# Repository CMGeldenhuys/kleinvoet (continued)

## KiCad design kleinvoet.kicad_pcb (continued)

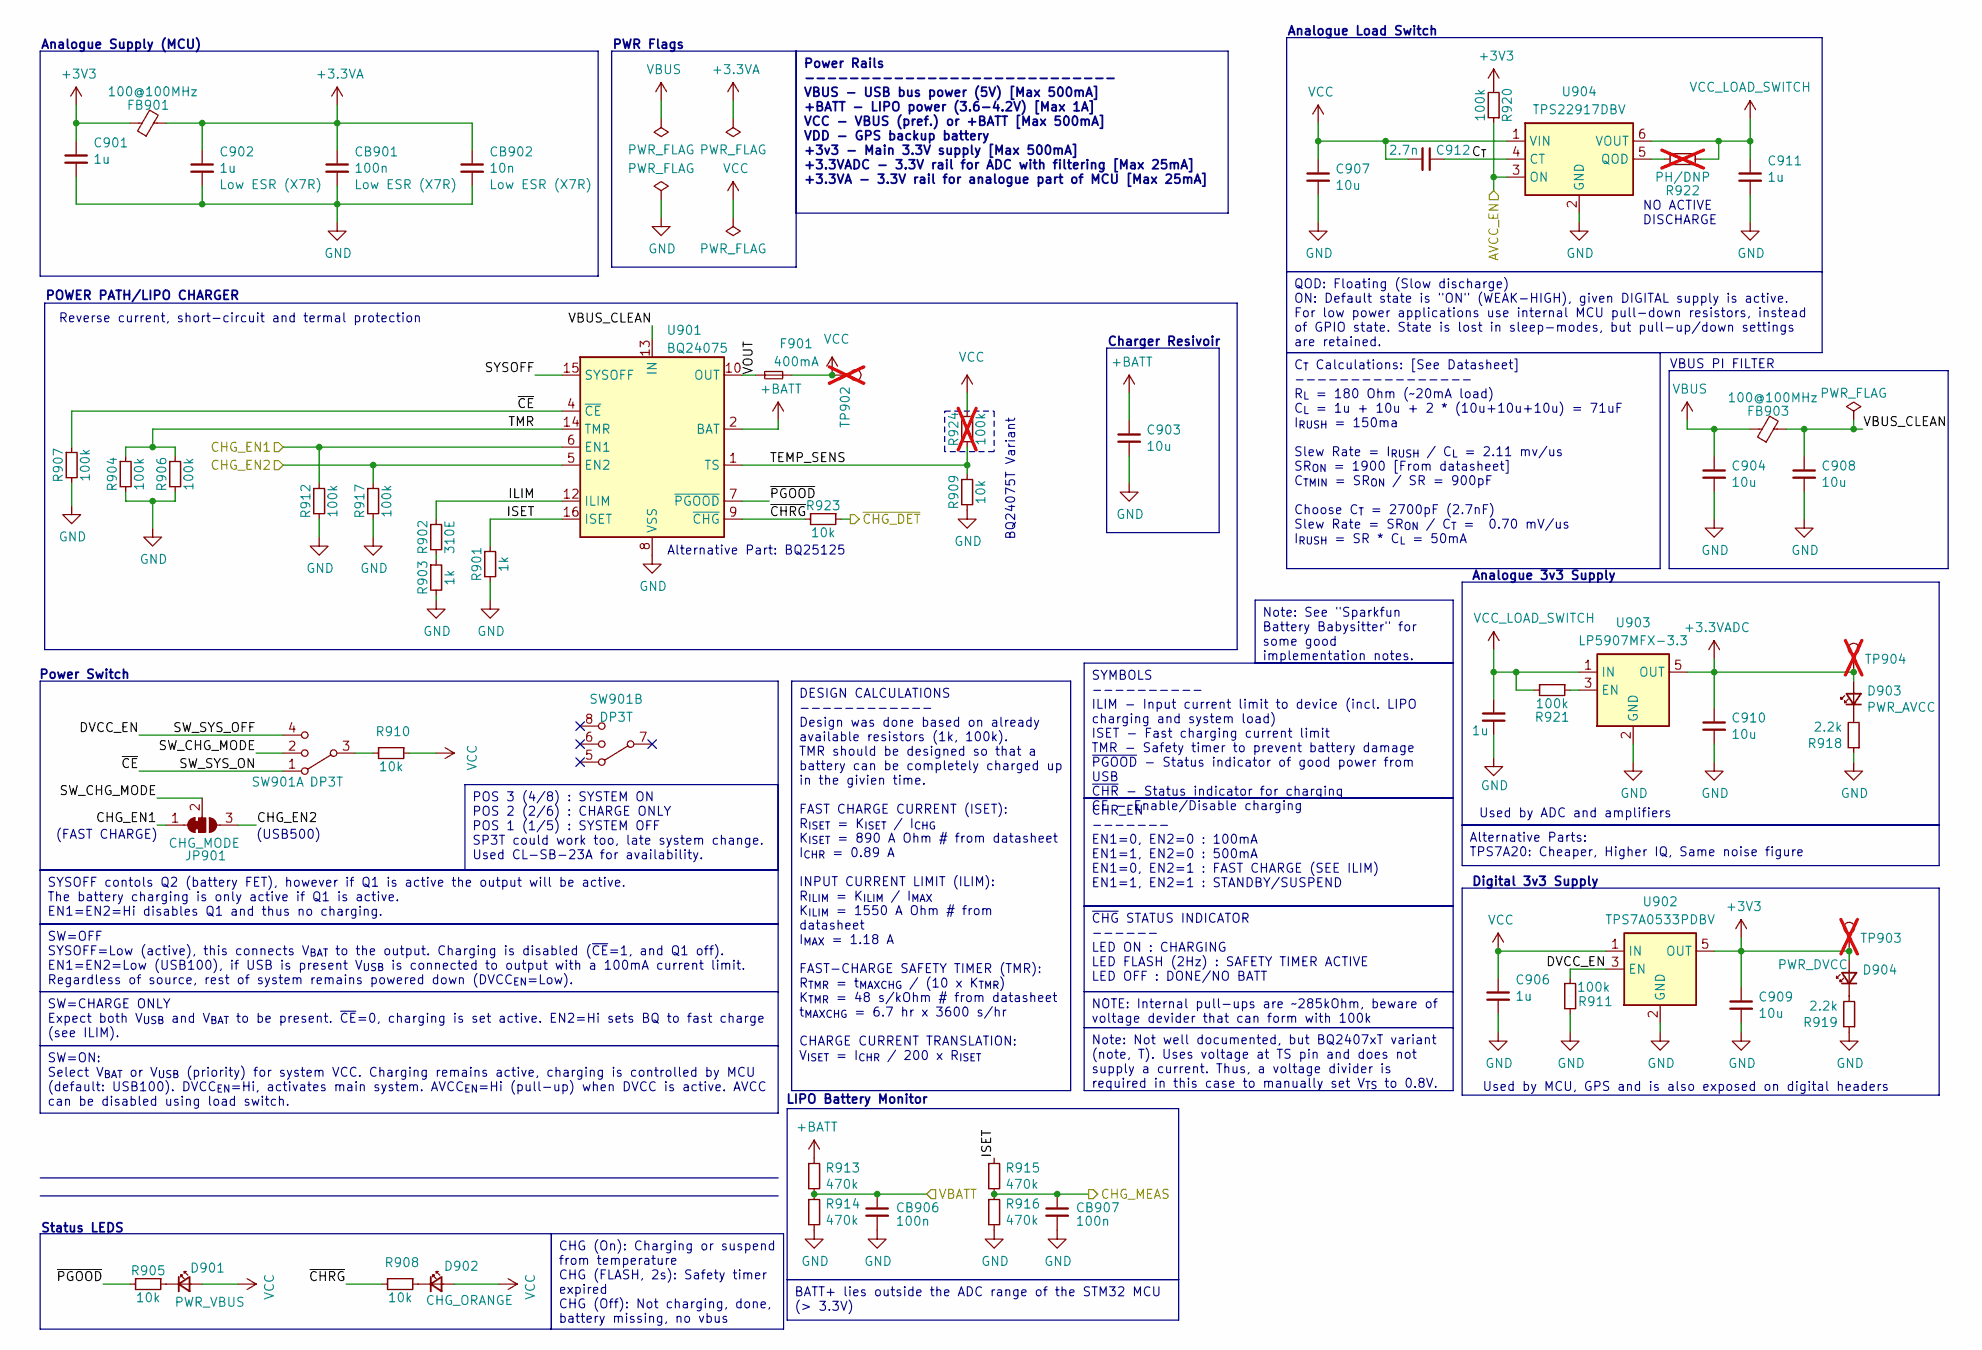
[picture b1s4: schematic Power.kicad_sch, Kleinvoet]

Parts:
C901, C902, C905, C906, C911: 1u; C_0402_1005Metric; MPN C0402C105K9PACTU
C903, C904, C907, C908, C909, C910: 10u; C_0402_1005Metric; MPN GRM155R60J106ME05D
C912: 2.7n; C_0402_1005Metric; MPN GRM1555C1H272GE01D
CB901, CB906, CB907: 100n; C_0402_1005Metric; MPN C0402C104K8PACTU
CB902: 10n; C_0402_1005Metric; MPN C0402C103K3RAC7411
D901: PWR_VBUS; LED_0603_1608Metric; MPN SML-D12U8WT86C
D902: CHG_ORANGE; LED_0603_1608Metric; MPN SML-D12D8WT86C
D903: PWR_AVCC; LED_0603_1608Metric; MPN SML-D12U8WT86C
D904: PWR_DVCC; LED_0603_1608Metric; MPN SML-D12U8WT86C
F901: 400mA; Fuse_0603_1608Metric_Pad1.05x0.95mm_HandSolder; MPN 0ZCM0020FF2G
FB901, FB903: 100@100MHz; L_0402_1005Metric; MPN BLM15HD102SN1D
JP901: CHG_MODE; SolderJumper-3_P1.3mm_Bridged12_RoundedPad1.0x1.5mm_NumberL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
R901, R903: 1k; R_0402_1005Metric; MPN RT0402FRE071KL
R902: 310E; R_0402_1005Metric; MPN RT0402FRE07309RL
R904, R906, R907, R911, R912, R917, R920, R921: 100k; R_0402_1005Metric; MPN RT0402FRE07100KL
R905, R908, R909, R910, R923: 10k; R_0402_1005Metric; MPN RT0402FRE1310KL
R913, R914, R915, R916: 470k; R_0603_1608Metric; MPN RC0603FR-07470KL
R918, R919: 2.2k; R_0402_1005Metric; MPN RT0402FRE072K2L
R922: PH/DNP; R_0402_1005Metric; not fitted
R924: 100k; R_0402_1005Metric; MPN RT0402FRE07100KL; not fitted
SW901: DP3T; SW_DP3T_Nidec-Cobal_CL-SB-23A; MPN CL-SB-23A-11T
TP902: V_OUT; TestPoint_Pad_D1.0mm; not fitted
TP903: 3V3_DIGITAL; TestPoint_Pad_D1.0mm; not fitted
TP904: 3v3_ANALOG; TestPoint_Pad_D1.0mm; not fitted
U901: BQ24075; VQFN-16-1EP_3x3mm_P0.5mm_EP1.68x1.68mm_ThermalVias; MPN BQ24075RGTR
U902: TPS7A0533PDBV; SOT-23-5; MPN TPS7A0533PDBVR
U903: LP5907MFX-3.3; SOT-23-5; MPN LP5907MFX-3.3/NOPB
U904: TPS22917DBV; SOT-23-6; MPN TPS22917DBVR

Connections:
+3.3VA: C902.1, CB901.1, CB902.1, FB901.2; also elsewhere on the board
+3.3VADC: C910.1, D903.2 (A), TP904.1, U903.5 (OUT); also elsewhere on the board
+BATT: C903.1, R913.1, U901.2 (BAT), U901.3 (BAT); also elsewhere on the board
/AVCC_EN: R920.1, U904.3 (ON); also elsewhere on the board
/BATT_~CHG: R923.1; also elsewhere on the board
/CHARGE_EN1: JP901.1 (A), R912.1, U901.6 (EN1); also elsewhere on the board
/CHARGE_EN2: JP901.3 (B), R917.1, U901.5 (EN2); also elsewhere on the board
/I_CHARGE: CB907.1, R915.2, R916.1; also elsewhere on the board
/Power/C_{T}: C912.1, U904.4 (CT)
/Power/DVCC_EN: R911.1, SW901.4, U902.3 (EN)
/Power/ILIM: R902.1, U901.12 (ILIM)
/Power/ISET: R901.1, R915.1, U901.16 (ISET)
/Power/SW_CHG_MODE: JP901.2 (C), SW901.2
/Power/SW_SYS_ON: R907.1, SW901.1, U901.4 (~CE)
/Power/SYSOFF: U901.15 (SYSOFF)
/Power/TEMP_SENS: R909.1, R924.2, U901.1 (TS)
/Power/TMR: R904.1, R906.1, U901.14 (TMR)
/Power/VBUS_CLEAN: C908.1, FB903.2, U901.13 (IN)
/Power/VOUT: F901.1, U901.10 (OUT), U901.11 (OUT)
/Power/~CHRG: R908.2, R923.2, U901.9 (~CHG)
/Power/~PGOOD: R905.2, U901.7 (~PGOOD)
/V_MONITOR: CB906.1, R913.2, R914.1; also elsewhere on the board
GND: C901.2, C902.2, C903.2, C904.2, C905.2, C906.2, C907.2, C908.2, C909.2, C910.2, C911.2, CB901.2, CB902.2, CB906.2, CB907.2, R901.2, R903.2, R904.2, R906.2, R907.2, R909.2, R911.2, R912.2, R914.2, R916.2, R917.2, R918.1, R919.1, U901.8 (VSS), U901.17 (VSS), U902.2 (GND), U903.2 (GND), U904.2 (GND); also elsewhere on the board
unnamed: D901.1 (K), R905.1
unnamed: D902.1 (K), R908.1
unnamed: D903.1 (K), R918.2
unnamed: D904.1 (K), R919.2
unnamed: R902.2, R903.1
unnamed: R910.2, SW901.3
unnamed: R921.1, U903.3 (EN)
unnamed: R922.1, U904.5 (QOD)
VBUS: C904.1, FB903.1; also elsewhere on the board
VCC: C906.1, C907.1, C912.2, D901.2 (A), D902.2 (A), F901.2, R910.1, R924.1, TP902.1, U902.1 (IN), U904.1 (VIN); also elsewhere on the board
VCC_LOAD_SWITCH: C905.1, C911.1, R921.2, R922.2, U903.1 (IN), U904.6 (VOUT); also elsewhere on the board

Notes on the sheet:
Status LEDS
Analogue Load Switch
Charger Resivoir
VBUS PI FILTER
Reverse current, short-circuit and termal protection
Power Switch
Digital 3v3 Supply
(FAST CHARGE)
LIPO Battery Monitor
Alternative Part: BQ25125
NO ACTIVE DISCHARGE
Analogue 3v3 Supply
PWR Flags
BQ24075T Variant
Used by ADC and amplifiers
POWER PATH/LIPO CHARGER
(USB500)
Analogue Supply (MCU)
Used by MCU, GPS and is also exposed on digital headers
Note: Not well documented, but BQ2407xT variant (note, T). Uses voltage at TS pin and does not supply a current. Thus, a voltage divider is required in this case to manually set V_{TS} to 0.8V.
SYSOFF contols Q2 (battery FET), however if Q1 is active the output will be active. The battery charging is only active if Q1 is active. EN1=EN2=Hi disables Q1 and thus no charging.
QOD: Floating (Slow discharge) ON: Default state is "ON" (WEAK-HIGH), given DIGITAL supply is active. For low power applications use internal MCU pull-down resistors, instead of GPIO state. State is lost in sleep-modes, but pull-up/down settings are retained.
SW=ON: Select V_{BAT} or V_{USB} (priority) for system VCC. Charging remains active, charging is controlled by MCU (default: USB100). DVCC_{EN}=Hi, activates main system. AVCC_{EN}=Hi (pull-up) when DVCC is active. AVCC can be disabled using load switch.
CHR_EN ------- EN1=0, EN2=0 : 100mA EN1=1, EN2=0 : 500mA EN1=0, EN2=1 : FAST CHARGE (SEE ILIM) EN1=1, EN2=1 : STANDBY/SUSPEND
SW=CHARGE ONLY Expect both V_{USB} and V_{BAT} to be present. ~{CE}=0, charging is set active. EN2=Hi sets BQ to fast charge (see ILIM).
DESIGN CALCULATIONS ------------ Design was done based on already available resistors (1k, 100k). TMR should be designed so that a battery can be completely charged up in the givien time. FAST CHARGE CURRENT (ISET): R_{ISET} = K_{ISET} / I_{CHG} K_{ISET} = 890 A Ohm # from datasheet I_{CHR} = 0.89 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
Note: See "Sparkfun Battery Babysitter" for some good implementation notes.
POS 3 (4/8) : SYSTEM ON POS 2 (2/6) : CHARGE ONLY POS 1 (1/5) : SYSTEM OFF SP3T could work too, late system change. Used CL-SB-23A for availability.
Alternative Parts: TPS7A20: Cheaper, Higher IQ, Same noise figure
~{CHG} STATUS INDICATOR ------ LED ON : CHARGING LED FLASH (2Hz) : SAFETY TIMER ACTIVE LED OFF : DONE/NO BATT
CHG (On): Charging or suspend from temperature CHG (FLASH, 2s): Safety timer expired CHG (Off): Not charging, done, battery missing, no vbus
BATT+ lies outside the ADC range of the STM32 MCU (> 3.3V)
SW=OFF SYSOFF=Low (active), this connects V_{BAT} to the output. Charging is disabled (~{CE}=1, and Q1 off). EN1=EN2=Low (USB100), if USB is present V_{USB} is connected to output with a 100mA current limit. Regardless of source, rest of system remains powered down (DVCC_{EN}=Low).
C_{T} Calculations: [See Datasheet] ---------------- R_{L} = 180 Ohm (~20mA load) C_{L} = 1u + 10u + 2 * (10u+10u+10u) = 71uF I_{RUSH} = 150ma Slew Rate = I_{RUSH} / C_{L} = 2.11 mv/us SR_{ON} = 1900 [From datasheet] C_{T}_{MIN} = SR_{ON} / SR = 900pF Choose C_{T} = 2700pF (2.7nF) Slew Rate = SR_{O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
NOTE: Internal pull-ups are ~285kOhm, beware of voltage devider that can form with 100k
SYMBOLS ---------- ILIM - Input current limit to device (incl. LIPO charging and system load) ISET - Fast charging current limit TMR - Safety timer to prevent battery damage ~{PGOOD} - Status indicator of good power from USB ~{CHR} - Status indicator for charging ~{CE} - Enable/Disable charging
Power Rails ---------------------------- VBUS - USB bus power (5V) [Max 500mA] +BATT - LIPO power (3.6-4.2V) [Max 1A] VCC - VBUS (pref.) or +BATT [Max 500mA] VDD - GPS backup battery +3v3 - Main 3.3V supply [Max 500mA] +3.3VADC - 3.3V rail for ADC with filtering [Max 25mA] +3.3VA - 3.3V rail for an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

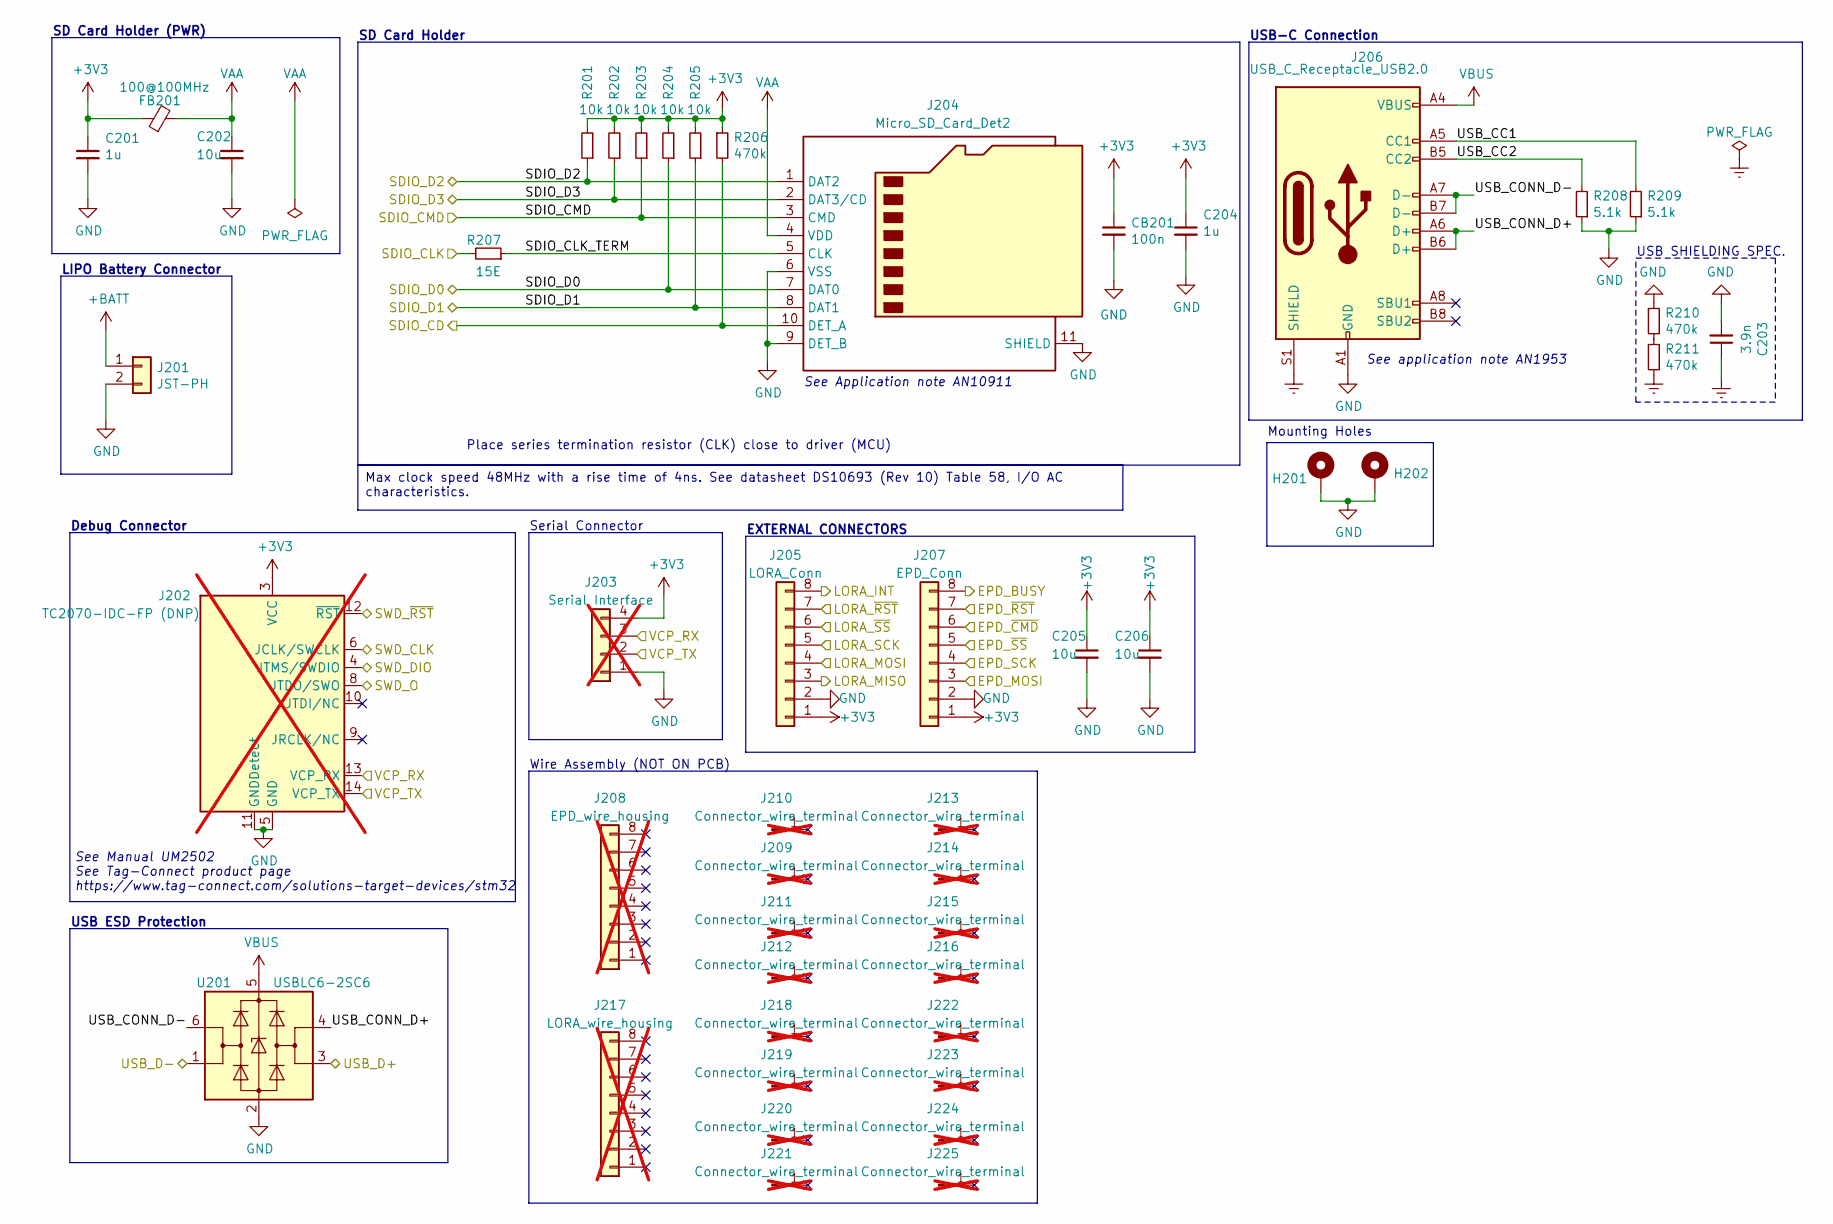
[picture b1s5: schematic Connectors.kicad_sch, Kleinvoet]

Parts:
C201, C204: 1u; C_0402_1005Metric; MPN C0402C105K9PACTU
C202, C205, C206: 10u; C_0402_1005Metric; MPN GRM155R60J106ME05D
C203: 3.9n; C_0402_1005Metric; MPN GRM1555C1H392GE01D
CB201: 100n; C_0402_1005Metric; MPN C0402C104K8PACTU
FB201: 100@100MHz; L_0402_1005Metric; MPN BLM15HD102SN1D
H201, H202: MountingHole_Pad; MountingHole_3.2mm_M3_Pad_Via
J201: JST-PH; JST_PH_S2B-PH-SM4-TB_1x02-1MP_P2.00mm_Horizontal; MPN 1769
J202: TC2070-IDC-FP (DNP); Tag-Connect_TC2070-IDC-FP_2x07_P1.27mm_Vertical; MPN TC2070-IDC-050; not fitted
J203: Serial Interface; PinHeader_1x04_P1.27mm_Vertical; not fitted
J204: Micro_SD_Card_Det2; microSD_HC_Molex_5031821852; MPN 503182-1852
J205: LORA_Conn; Connector_Amphenol_10114828-xxx08LF_Vertical; MPN 10114828-11108LF
J206: USB_C_Receptacle_USB2.0; USB_C_Recepetacle_JAE_DX07S016JA1; MPN DX07S016JA1R1500
J207: EPD_Conn; Connector_Amphenol_10114828-xxx08LF_Vertical; MPN 10114828-11108LF
J208: EPD_wire_housing; MPN 10114826-00008LF; not fitted
J209, J210, J211, J212, J213, J214, J215, J216, J218, J219, J220, J221, J222, J223, J224, J225: Connector_wire_terminal; MPN 10114827-002LF; not fitted
J217: LORA_wire_housing; MPN 10114826-00008LF; not fitted
R201, R202, R203, R204, R205: 10k; R_0402_1005Metric; MPN RT0402FRE1310KL
R206, R210, R211: 470k; R_0603_1608Metric; MPN RC0603FR-07470KL
R207: 15E; R_0402_1005Metric; MPN RT0402FRE0715RL
R208, R209: 5.1k; R_0603_1608Metric; MPN AC0603FR-135K1L
U201: USBLC6-2SC6; SOT-666_Handsoldering; MPN USBLC6-2P6

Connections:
+BATT: J201.1; also elsewhere on the board
/BOOT1: J205.6; also elsewhere on the board
/CONN_MISO: J205.4; also elsewhere on the board
/CONN_MOSI: J205.3, J207.3; also elsewhere on the board
/CONN_SCK: J205.5, J207.4; also elsewhere on the board
/Connectors/SDIO_CLK_TERM: J204.5 (CLK), R207.1
/Connectors/USB_CC1: J206.A5 (CC1), R209.2
/Connectors/USB_CC2: J206.B5 (CC2), R208.2
/Connectors/USB_CONN_D+: J206.A6 (D+), J206.B6 (D+), U201.4 (I/O2)
/Connectors/USB_CONN_D-: J206.A7 (D-), J206.B7 (D-), U201.6 (I/O1)
/EPD_BUSY: J207.8; also elsewhere on the board
/EPD_~CMD: J207.6; also elsewhere on the board
/EPD_~RST: J207.7; also elsewhere on the board
/EPD_~SS: J207.5; also elsewhere on the board
/LORA_INT: J205.8; also elsewhere on the board
/LORA_~RST: J205.7; also elsewhere on the board
/SDIO_CD: J204.10 (DET_A), R206.2; also elsewhere on the board
/SDIO_CLK: R207.2; also elsewhere on the board
/SDIO_CMD: J204.3 (CMD), R203.1; also elsewhere on the board
/SDIO_D0: J204.7 (DAT0), R204.1; also elsewhere on the board
/SDIO_D1: J204.8 (DAT1), R205.1; also elsewhere on the board
/SDIO_D2: J204.1 (DAT2), R201.1; also elsewhere on the board
/SDIO_D3: J204.2 (DAT3/CD), R202.1; also elsewhere on the board
/SWCLK: J202.6 (JCLK/SWCLK); also elsewhere on the board
/SWDIO: J202.4 (JTMS/SWDIO); also elsewhere on the board
/SWO: J202.8 (JTDO/SWO); also elsewhere on the board
/USB_DN: U201.1 (I/O1); also elsewhere on the board
/USB_DP: U201.3 (I/O2); also elsewhere on the board
/VCP_RX: J202.13 (VCP_RX), J203.3; also elsewhere on the board
/VCP_TX: J202.14 (VCP_TX), J203.2; also elsewhere on the board
/~RST: J202.12 (~RST); also elsewhere on the board
Earth: C203.1, J206.S1 (SHIELD), R211.2
GND: C201.2, C202.2, C203.2, C204.2, C205.2, C206.2, CB201.2, H201.1, H202.1, J201.2, J202.5 (GND), J202.7 (GND), J202.11 (GNDDetect), J203.1, J204.6 (VSS), J204.9 (DET_B), J204.11 (SHIELD), J205.2, J206.A1 (GND), J206.A12 (GND), J206.B1 (GND), J206.B12 (GND), J207.2, R208.1, R209.1, R210.1, U201.2 (GND); also elsewhere on the board
unnamed: R210.2, R211.1
VAA: C202.1, FB201.2, J204.4 (VDD)
VBUS: J206.A4 (VBUS), J206.A9 (VBUS), J206.B4 (VBUS), J206.B9 (VBUS), U201.5 (VBUS); also elsewhere on the board

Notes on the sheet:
USB ESD Protection
Mounting Holes
Debug Connector
Place series termination resistor (CLK) close to driver (MCU)
Serial Connector
Wire Assembly (NOT ON PCB)
See application note AN1953
See Manual UM2502 See Tag-Connect product page https://www.tag-connect.com/solutions-target-devices/stm32
EXTERNAL CONNECTORS
See Application note AN10911
USB SHIELDING SPEC.
SD Card Holder (PWR)
LIPO Battery Connector
SD Card Holder
USB-C Connection
Max clock speed 48MHz with a rise time of 4ns. See datasheet DS10693 (Rev 10) Table 58, I/O AC characteristics.

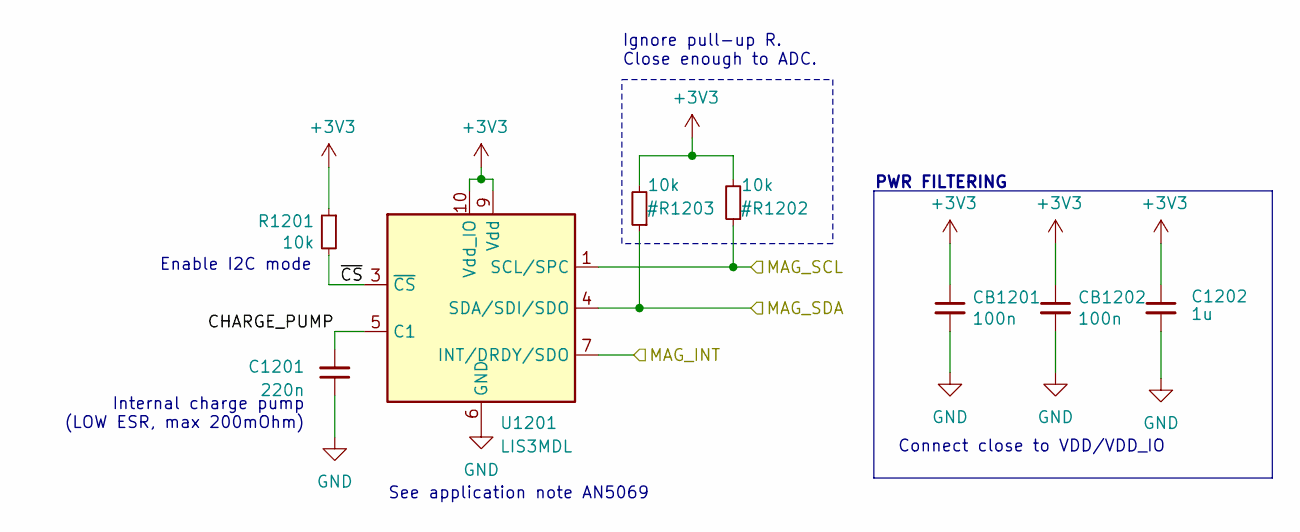
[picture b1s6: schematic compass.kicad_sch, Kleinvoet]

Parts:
C1201: 220n; C_0402_1005Metric_Pad0.74x0.62mm_HandSolder; MPN GRT155R71A224KE01D
C1202: 1u; C_0402_1005Metric; MPN C0402C105K9PACTU
CB1201, CB1202: 100n; C_0402_1005Metric; MPN C0402C104K8PACTU
R1201: 10k; R_0402_1005Metric; MPN RT0402FRE1310KL
U1201: LIS3MDL; LIS3MDL_LGA-12_2x2mm_P0.5mm; MPN LIS3MDLTR

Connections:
/CompassMagnetometer/CHARGE_PUMP: C1201.2, U1201.5 (C1)
/CompassMagnetometer/~CS: R1201.2, U1201.3 (~CS)
/MAG_INT: U1201.7 (INT/DRDY/SDO); also elsewhere on the board
GND: C1201.1, C1202.2, CB1201.2, CB1202.2, U1201.2 (NC/GND), U1201.6 (GND), U1201.8 (GND), U1201.11 (NC/GND), U1201.12 (NC/GND); also elsewhere on the board

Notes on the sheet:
Internal charge pump (LOW ESR, max 200mOhm)
See application note AN5069
Ignore pull-up R. Close enough to ADC.
Connect close to VDD/VDD_IO
Enable I2C mode
PWR FILTERING

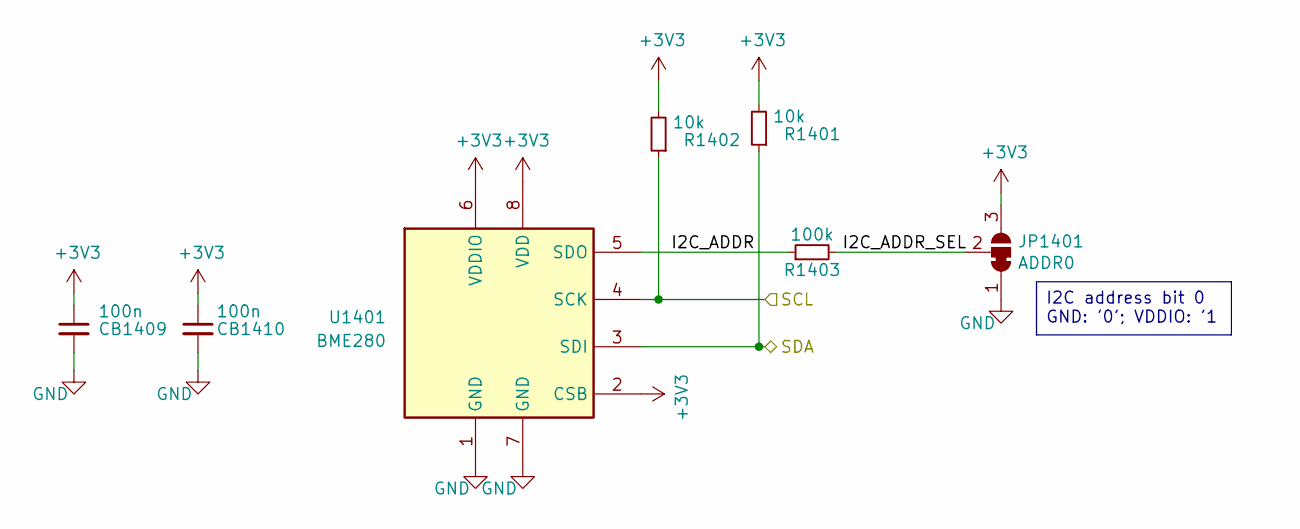
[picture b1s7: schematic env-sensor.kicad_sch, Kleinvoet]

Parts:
CB1409, CB1410: 100n; C_0402_1005Metric; MPN C0402C104K8PACTU
JP1401: ADDR0; SolderJumper-3_P1.3mm_Bridged12_RoundedPad1.0x1.5mm_NumberL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
R1401, R1402: 10k; R_0402_1005Metric; MPN RT0402FRE1310KL
R1403: 100k; R_0402_1005Metric; MPN RT0402FRE07100KL
U1401: BME280; Bosch_LGA-8_2.5x2.5mm_P0.65mm_ClockwisePinNumbering; MPN BME280

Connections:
/EnviromentalSensor/I2C_ADDR: R1403.1, U1401.5 (SDO)
/EnviromentalSensor/I2C_ADDR_SEL: JP1401.2 (C), R1403.2
GND: CB1409.2, CB1410.2, JP1401.1 (A), U1401.1 (GND), U1401.7 (GND); also elsewhere on the board

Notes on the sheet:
I2C address bit 0 GND: '0'; VDDIO: '1

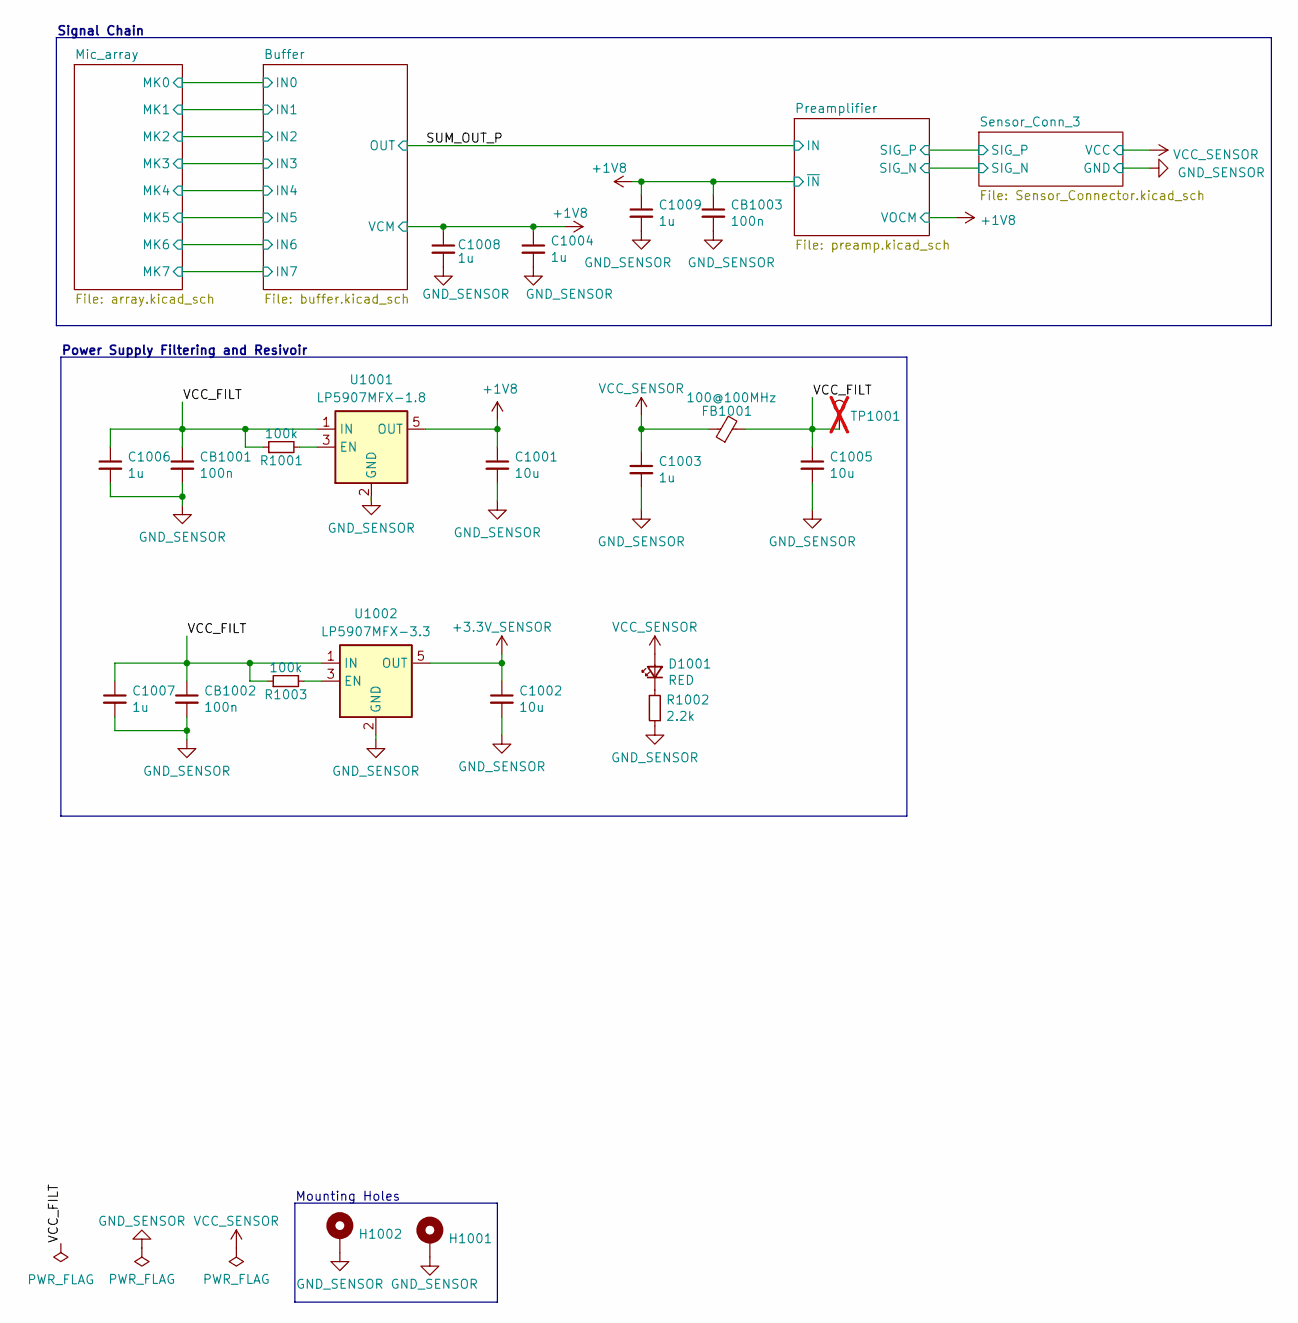
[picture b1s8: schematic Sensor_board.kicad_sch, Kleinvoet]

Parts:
C1001, C1002, C1005: 10u; C_0402_1005Metric; MPN GRM155R60J106ME05D
C1003, C1004, C1006, C1007, C1008, C1009: 1u; C_0402_1005Metric; MPN C0402C105K9PACTU
CB1001, CB1002, CB1003: 100n; C_0402_1005Metric; MPN C0402C104K8PACTU
D1001: RED; LED_0603_1608Metric; MPN SML-D12U8WT86C
FB1001: 100@100MHz; L_0402_1005Metric; MPN BLM15HD102SN1D
H1001, H1002: MountingHole_Pad; MountingHole_3.2mm_M3_Pad_Via
R1001, R1003: 100k; R_0402_1005Metric; MPN RT0402FRE07100KL
R1002: 2.2k; R_0402_1005Metric; MPN RT0402FRE072K2L
TP1001: VCC_Filt; TestPoint_Pad_D1.0mm; not fitted
U1001: LP5907MFX-1.8; SOT-23-5; MPN LP5907MFX-1.8/NOPB
U1002: LP5907MFX-3.3; SOT-23-5; MPN LP5907MFX-3.3/NOPB

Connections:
+1V8: C1001.1, C1004.1, C1008.1, C1009.1, CB1003.1, U1001.5 (OUT); also elsewhere on the board
+3.3V_SENSOR: C1002.1, U1002.5 (OUT); also elsewhere on the board
/Sensor_board/VCC_FILT: C1005.1, C1006.1, C1007.1, CB1001.1, CB1002.1, FB1001.2, R1001.1, R1003.1, TP1001.1, U1001.1 (IN), U1002.1 (IN)
GND_SENSOR: C1001.2, C1002.2, C1003.2, C1004.2, C1005.2, C1006.2, C1007.2, C1008.2, C1009.2, CB1001.2, CB1002.2, CB1003.2, H1001.1, H1002.1, R1002.2, U1001.2 (GND), U1002.2 (GND); also elsewhere on the board
unnamed: D1001.1 (K), R1002.1
unnamed: R1001.2, U1001.3 (EN)
unnamed: R1003.2, U1002.3 (EN)
VCC_SENSOR: C1003.1, D1001.2 (A), FB1001.1; also elsewhere on the board

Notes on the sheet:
Power Supply Filtering and Resivoir
Signal Chain
Mounting Holes

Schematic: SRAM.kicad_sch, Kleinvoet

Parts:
CB1301: 100n; C_0402_1005Metric; MPN C0402C104K8PACTU
R1301, R1302, R1303: 100k; R_0402_1005Metric; MPN RT0402FRE07100KL
U1301: 23LC1024-I/SN; SOIC-8_3.9x4.9mm_P1.27mm; MPN 23LC1024-I/SN

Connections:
/SRAM_MISO: U1301.2 (SO); also elsewhere on the board
/SRAM_MOSI: U1301.5 (SI); also elsewhere on the board
/SRAM_SCK: U1301.6 (SCK); also elsewhere on the board
GND: CB1301.2, R1303.2, U1301.4 (Vss); also elsewhere on the board
unnamed: R1301.2, U1301.3 (NU)
unnamed: R1303.1, U1301.1 (~CS)
unnamed: R1302.2, U1301.7 (~HOLD)

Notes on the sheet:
NU is pulled HIGH since we are only using SPI mode. ~{HOLD} is pulled HIGH, to disable transaction holding mode.
SPI Bus is not shared, and need the ~{SS} pin. So, keep always selected.

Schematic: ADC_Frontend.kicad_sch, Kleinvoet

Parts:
C701, C702: 220p; C_0402_1005Metric; MPN GRT1555C1H221FA02D
C703: 27n; C_0805_2012Metric; MPN GRM2165C1H273JA01D
C704: PH/DNP; C_0402_1005Metric; not fitted
C705, C712: 1u; C_0402_1005Metric; MPN C0402C105K9PACTU
C706, C707: 3.9n; C_0402_1005Metric; MPN GRM1555C1H392GE01D
C708: 100n; C_0402_1005Metric; MPN C0402C104K8PACTU
C709, C711: 10n; C_0402_1005Metric; MPN GRM1555CYA103GE01D
C710: 100n; C_1206_3216Metric; MPN GRM3195C1H104JA05D
R701, R702: 310E; R_0402_1005Metric; MPN RT0402FRE07309RL
R703, R704: 330E; R_0402_1005Metric; MPN RT0402FRE07330RL
R705, R706: 360E; R_0402_1005Metric; MPN RT0402FRE07360RL
R707, R708: 15E; R_0402_1005Metric; MPN RT0402FRE0715RL
R709, R710: 47E; R_0402_1005Metric; MPN RT0402FRE0747RL
U701: THS4551xRGT; VQFN-16-1EP_3x3mm_P0.5mm_EP1.68x1.68mm_ThermalVias; MPN THS4551IRGTR

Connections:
+3.3VADC: C708.2, C712.1, U701.5 (VS+), U701.6 (VS+), U701.7 (VS+), U701.8 (VS+), U701.12 (~PD); also elsewhere on the board
/ADC_Interface/ADC_1_N: C710.2, C711.1, R710.1; also elsewhere on the board
/ADC_Interface/ADC_1_P: C709.2, C710.1, R709.1; also elsewhere on the board
/ADC_Interface/ADC_AA_1/FB: C706.1, U701.4 (FB+)
/ADC_Interface/ADC_AA_1/FB_N: C701.1, C703.2, R701.1, R703.2, R705.2
/ADC_Interface/ADC_AA_1/FB_P: C702.1, C703.1, R702.1, R704.2, R706.2
/ADC_Interface/ADC_AA_1/IN: C704.1, C707.2, R704.1, U701.2 (IN+)
/ADC_Interface/ADC_AA_1/OUT: R707.2, U701.10 (OUT+)
/ADC_Interface/ADC_AA_1/OUT_DRIVER: R705.1, R707.1, R709.2
/ADC_Interface/ADC_AA_1/~FB: C707.1, U701.1 (FB-)
/ADC_Interface/ADC_AA_1/~IN: C704.2, C706.2, R703.1, U701.3 (IN-)
/ADC_Interface/ADC_AA_1/~OUT_DRIVER: R706.1, R708.1, R710.2
/ADC_Interface/ADC_AA_1/~OUT: R708.2, U701.11 (OUT-)
/ADC_Interface/ADC_PORT_1_SIG_N: R701.2; also elsewhere on the board
/ADC_Interface/ADC_PORT_1_SIG_P: R702.2; also elsewhere on the board
/ADC_Interface/VCM: C705.1, U701.9 (VOCM); also elsewhere on the board
GND: C701.2, C702.2, C705.2, C708.1, C709.1, C711.2, C712.2, U701.13 (VS-), U701.14 (VS-), U701.15 (VS-), U701.16 (VS-), U701.17 (EP); also elsewhere on the board

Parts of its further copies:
C801, C802: 220p; C_0402_1005Metric; MPN GRT1555C1H221FA02D
C803: 27n; C_0805_2012Metric; MPN GRM2165C1H273JA01D
C804: PH/DNP; C_0402_1005Metric; not fitted
C805, C812: 1u; C_0402_1005Metric; MPN C0402C105K9PACTU
C806, C807: 3.9n; C_0402_1005Metric; MPN GRM1555C1H392GE01D
C808: 100n; C_0402_1005Metric; MPN C0402C104K8PACTU
C809, C811: 10n; C_0402_1005Metric; MPN GRM1555CYA103GE01D
C810: 100n; C_1206_3216Metric; MPN GRM3195C1H104JA05D
R801, R802: 310E; R_0402_1005Metric; MPN RT0402FRE07309RL
R803, R804: 330E; R_0402_1005Metric; MPN RT0402FRE07330RL
R805, R806: 360E; R_0402_1005Metric; MPN RT0402FRE07360RL
R807, R808: 15E; R_0402_1005Metric; MPN RT0402FRE0715RL
R809, R810: 47E; R_0402_1005Metric; MPN RT0402FRE0747RL
U801: THS4551xRGT; VQFN-16-1EP_3x3mm_P0.5mm_EP1.68x1.68mm_ThermalVias; MPN THS4551IRGTR

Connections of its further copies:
+3.3VADC: C808.2, C812.1, U801.5 (VS+), U801.6 (VS+), U801.7 (VS+), U801.8 (VS+), U801.12 (~PD); also elsewhere on the board
/ADC_Interface/ADC_2_N: C810.2, C811.1, R810.1; also elsewhere on the board
/ADC_Interface/ADC_2_P: C809.2, C810.1, R809.1; also elsewhere on the board
/ADC_Interface/ADC_AA_2/FB: C806.1, U801.4 (FB+)
/ADC_Interface/ADC_AA_2/FB_N: C801.1, C803.2, R801.1, R803.2, R805.2
/ADC_Interface/ADC_AA_2/FB_P: C802.1, C803.1, R802.1, R804.2, R806.2
/ADC_Interface/ADC_AA_2/IN: C804.1, C807.2, R804.1, U801.2 (IN+)
/ADC_Interface/ADC_AA_2/OUT: R807.2, U801.10 (OUT+)
/ADC_Interface/ADC_AA_2/OUT_DRIVER: R805.1, R807.1, R809.2
/ADC_Interface/ADC_AA_2/~FB: C807.1, U801.1 (FB-)
/ADC_Interface/ADC_AA_2/~IN: C804.2, C806.2, R803.1, U801.3 (IN-)
/ADC_Interface/ADC_AA_2/~OUT_DRIVER: R806.1, R808.1, R810.2
/ADC_Interface/ADC_AA_2/~OUT: R808.2, U801.11 (OUT-)
/ADC_Interface/ADC_PORT_2_SIG_N: R801.2; also elsewhere on the board
/ADC_Interface/ADC_PORT_2_SIG_P: R802.2; also elsewhere on the board
/ADC_Interface/VCM: C805.1, U801.9 (VOCM); also elsewhere on the board
GND: C801.2, C802.2, C805.2, C808.1, C809.1, C811.2, C812.2, U801.13 (VS-), U801.14 (VS-), U801.15 (VS-), U801.16 (VS-), U801.17 (EP); also elsewhere on the board

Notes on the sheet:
ADC inrush comp.
Line RX + ADC Drive
CONNECTED INTERNALLY
Incase addtional input capacitance is required. Use for osc. and HF pole compensation.
PCB layout done from TI Reference design, TIDA-01013 PCB When "inside" filter area use short and thin traces to reduce coupling. "Outside" use 50Ohm control impedance traces. Differenctial traces aren't required, however ENSURE THAT THE IMPEDANCES ARE MATCHED.
Alternative part: OPA1632 Lower cost, designed for audio bandwidth, lower THD, lower bandwidth However, input stage is super-beta, in other words low noise but 2Vbe input voltage required. Input voltage swing is thus +-1V from rails.

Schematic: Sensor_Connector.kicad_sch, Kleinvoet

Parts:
C501, C502: 220p; C_0402_1005Metric; MPN GRT1555C1H221FA02D
FB501, FB502: 1k@100MHz; L_0402_1005Metric; MPN BLM15AX102SZ1D
J501: Sensor_conn; Connector_Amphenol_10114828-xxx04LF_Vertical; MPN 10114828-11104LF
J502: Sensor_wire_housing; MPN 10114826-00004LF; not fitted
J503, J504, J505, J506: Connector_wire_terminal; MPN 10114827-002LF; not fitted
R501: PH/DNP; R_0402_1005Metric; not fitted

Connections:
/ADC_Interface/ADC_PORT_1_SIG_N: C502.2, FB502.2; also elsewhere on the board
/ADC_Interface/ADC_PORT_1_SIG_P: C501.1, FB501.2; also elsewhere on the board
/ADC_Interface/Sensor_Conn_1/SIG_CONN_N: FB502.1, J501.1, R501.2
/ADC_Interface/Sensor_Conn_1/SIG_CONN_P: FB501.1, J501.2, R501.1
GND: C501.2, C502.1, J501.3; also elsewhere on the board
VCC_LOAD_SWITCH: J501.4; also elsewhere on the board

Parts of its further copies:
C601, C602, C1101, C1102: 220p; C_0402_1005Metric; MPN GRT1555C1H221FA02D
FB601, FB602, FB1101, FB1102: 1k@100MHz; L_0402_1005Metric; MPN BLM15AX102SZ1D
J601, J1101: Sensor_conn; Connector_Amphenol_10114828-xxx04LF_Vertical; MPN 10114828-11104LF
R601, R1101: PH/DNP; R_0402_1005Metric; not fitted

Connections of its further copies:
/ADC_Interface/ADC_PORT_2_SIG_N: C602.2, FB602.2; also elsewhere on the board
/ADC_Interface/ADC_PORT_2_SIG_P: C601.1, FB601.2; also elsewhere on the board
/ADC_Interface/Sensor_Conn_2/SIG_CONN_N: FB602.1, J601.1, R601.2
/ADC_Interface/Sensor_Conn_2/SIG_CONN_P: FB601.1, J601.2, R601.1
/Sensor_board/Preamplifier/SIG_N: C1102.2, FB1102.2; also elsewhere on the board
/Sensor_board/Preamplifier/SIG_P: C1101.1, FB1101.2; also elsewhere on the board
/Sensor_board/Sensor_Conn_3/SIG_CONN_N: FB1102.1, J1101.1, R1101.2
/Sensor_board/Sensor_Conn_3/SIG_CONN_P: FB1101.1, J1101.2, R1101.1
GND: C601.2, C602.1, J601.3; also elsewhere on the board
GND_SENSOR: C1101.2, C1102.1, J1101.3; also elsewhere on the board
VCC_LOAD_SWITCH: J601.4; also elsewhere on the board
VCC_SENSOR: J1101.4; also elsewhere on the board

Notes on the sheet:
Wire Assembly (NOT ON PCB)
Sensor Connector
Signal Conditioning

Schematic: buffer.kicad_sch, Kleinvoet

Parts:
C1502, C1610, C1611, C1612: 220p; C_0402_1005Metric; MPN GRT1555C1H221FA02D
C1504: 1u; C_0402_1005Metric; MPN C0402C105K9PACTU
C1608, C1609, C1613, C1614: > 22u; CP_EIA-1608-10_AVX-L; MPN F980G107MMAAH1
CB1502, CB1603, CB1604, CB1605, CB1606, CB1607, CB1608, CB1609, CB1610: 100n; C_0402_1005Metric; MPN C0402C104K8PACTU
R1514, R1609, R1610, R1611, R1612, R1613, R1614, R1615, R1616, R1624, R1629, R1634: 1k; R_0402_1005Metric; MPN RT0402FRE071KL
R1617, R1618, R1619, R1620, R1626, R1627, R1631, R1632: 330E; R_0402_1005Metric; MPN RT0402FRE07330RL
R1621, R1622, R1628, R1633: 10k; R_0402_1005Metric; MPN RT0402FRE1310KL
R1623, R1625, R1630, R1635: 15E; R_0402_1005Metric; MPN RT0402FRE0715RL
U1601: OPA1664; Texas_PW_R-PDSO-G14; MPN OPA1664AIPWR

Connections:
+1V8: CB1603.1, CB1604.1, CB1605.1, CB1606.1, CB1607.1, CB1608.1, CB1609.1, CB1610.1, R1617.2, R1618.2, R1619.2, R1620.2, R1621.1, R1622.1, R1626.2, R1627.2, R1628.1, R1631.2, R1632.2, R1633.1; also elsewhere on the board
+3.3V_SENSOR: C1504.1, CB1502.1, U1601.4 (V+); also elsewhere on the board
/Sensor_board/Buffer/IN0: R1609.1; also elsewhere on the board
/Sensor_board/Buffer/IN1: R1614.1; also elsewhere on the board
/Sensor_board/Buffer/IN2: R1611.1; also elsewhere on the board
/Sensor_board/Buffer/IN3: R1616.1; also elsewhere on the board
/Sensor_board/Buffer/IN4: R1610.1; also elsewhere on the board
/Sensor_board/Buffer/IN5: R1613.1; also elsewhere on the board
/Sensor_board/Buffer/IN6: R1612.1; also elsewhere on the board
/Sensor_board/Buffer/IN7: R1615.1; also elsewhere on the board
/Sensor_board/Buffer/PAIR_A: C1608.1, R1611.2, R1614.2
/Sensor_board/Buffer/PAIR_B: C1614.1, R1610.2, R1616.2
/Sensor_board/Buffer/PAIR_C: C1609.1, R1609.2, R1615.2
/Sensor_board/Buffer/PAIR_D: C1613.1, R1612.2, R1613.2
/Sensor_board/Buffer/PREAMP_A_FB: C1502.2, R1514.1, R1617.1, R1618.1, U1601.2 (~IN)
/Sensor_board/Buffer/PREAMP_A_OUT: C1502.1, R1514.2, R1623.2, U1601.1 (OUT)
/Sensor_board/Buffer/PREAMP_B_FB: C1610.2, R1619.1, R1620.1, R1624.1, U1601.6 (~IN)
/Sensor_board/Buffer/PREAMP_B_OUT: C1610.1, R1624.2, R1625.2, U1601.7 (OUT)
/Sensor_board/Buffer/PREAMP_C_FB: C1612.2, R1631.1, R1632.1, R1634.1, U1601.9 (~IN)
/Sensor_board/Buffer/PREAMP_C_OUT: C1612.1, R1634.2, R1635.2, U1601.8 (OUT)
/Sensor_board/Buffer/PREAMP_D_FB: C1611.2, R1626.1, R1627.1, R1629.1, U1601.13 (~IN)
/Sensor_board/Buffer/PREAMP_D_OUT: C1611.1, R1629.2, R1630.2, U1601.14 (OUT)
/Sensor_board/Buffer/SENS_ARRAY_A: C1608.2, R1621.2, U1601.3 (IN)
/Sensor_board/Buffer/SENS_ARRAY_B: C1614.2, R1622.2, U1601.5 (IN)
/Sensor_board/Buffer/SENS_ARRAY_C: C1609.2, R1633.2, U1601.10 (IN)
/Sensor_board/Buffer/SENS_ARRAY_D: C1613.2, R1628.2, U1601.12 (IN)
/Sensor_board/SUM_OUT_P: R1623.1, R1625.1, R1630.1, R1635.1; also elsewhere on the board
GND_SENSOR: C1504.2, CB1502.2, CB1603.2, CB1604.2, CB1605.2, CB1606.2, CB1607.2, CB1608.2, CB1609.2, CB1610.2, U1601.11 (V-); also elsewhere on the board

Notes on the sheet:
HPF
See application note: AN-1165 by Inversense
Sensor Summation
DC Bias (1.8V)
330/2 = 165 Ohm
Preamplifier
DC Removal (HPF)
OPA166X Filtering
DC Bias required due to single rail supply amplifier (approx. symetrical swing). According to the OPA1662 the VCM must be (Vss + 0.5) < Vcm < (Vcc - 1). (Vss=0V GND, Vcc=3v3) This is due to the bipolar input stage (Vbe = ~0.5V).
HPF = 1/(2pi*(N*22u)*10k) = ~0.04Hz (N=8) Use high CV capacitors such as tantalum. DO NOT USE MLCC X5 or X7. Ceramic capacitors have a dC/dV term. This will cause the capacitance to change with amplitude and create NL distortions. Futhermore, MLCCs act like microphones due to the piezo effect.
Parallel the amplieifers to lower noise.
HPF: Reduce loop gain at higher frequencies. Gain: Set by input resistance and feedback resistor Bias: To allow DC coupled operation IN: Resitor/Cap network used to balance input current, significant due to input topology of opamp
Passive sunmming results in no voltage gain. Each microphone capsule is loaded by ~1kOhm (1k + 1k/7). Summing can happen PRE or POST HPF. Pre-HPF, results in loading the DC signal by the equiv. input impedance, however since all DC voltage are approx. the same from each capsule, in reality the DC s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
